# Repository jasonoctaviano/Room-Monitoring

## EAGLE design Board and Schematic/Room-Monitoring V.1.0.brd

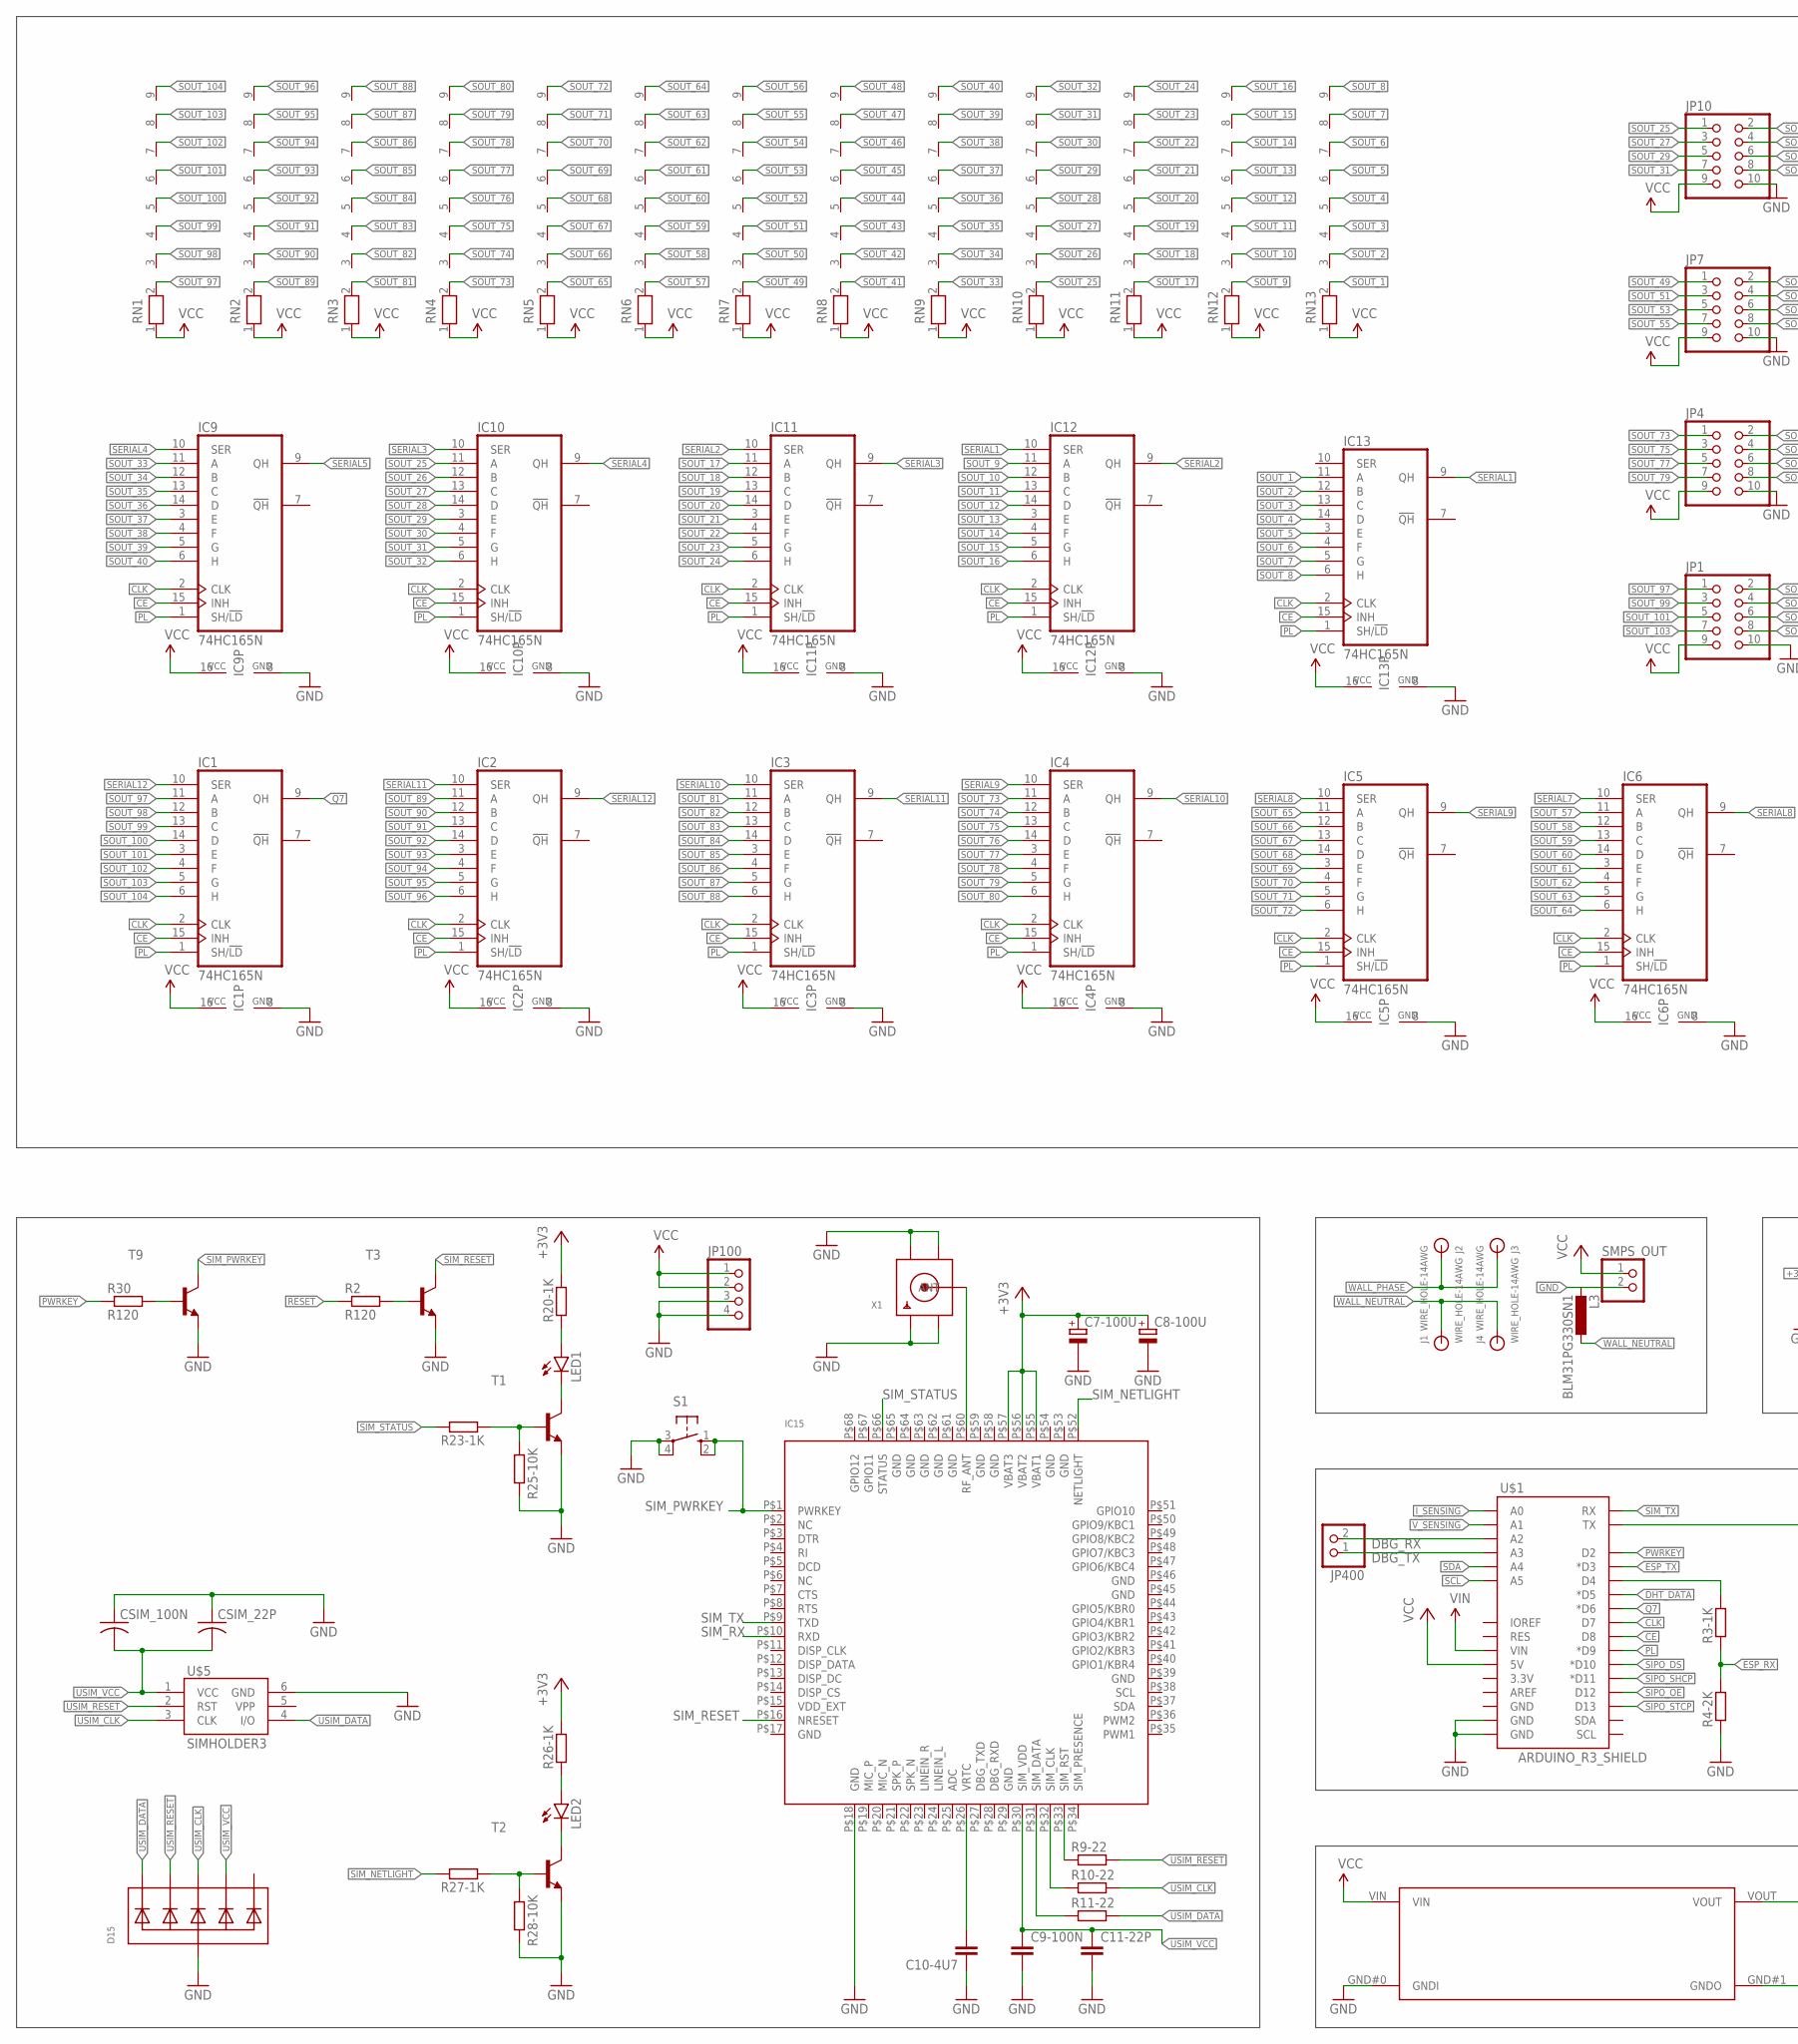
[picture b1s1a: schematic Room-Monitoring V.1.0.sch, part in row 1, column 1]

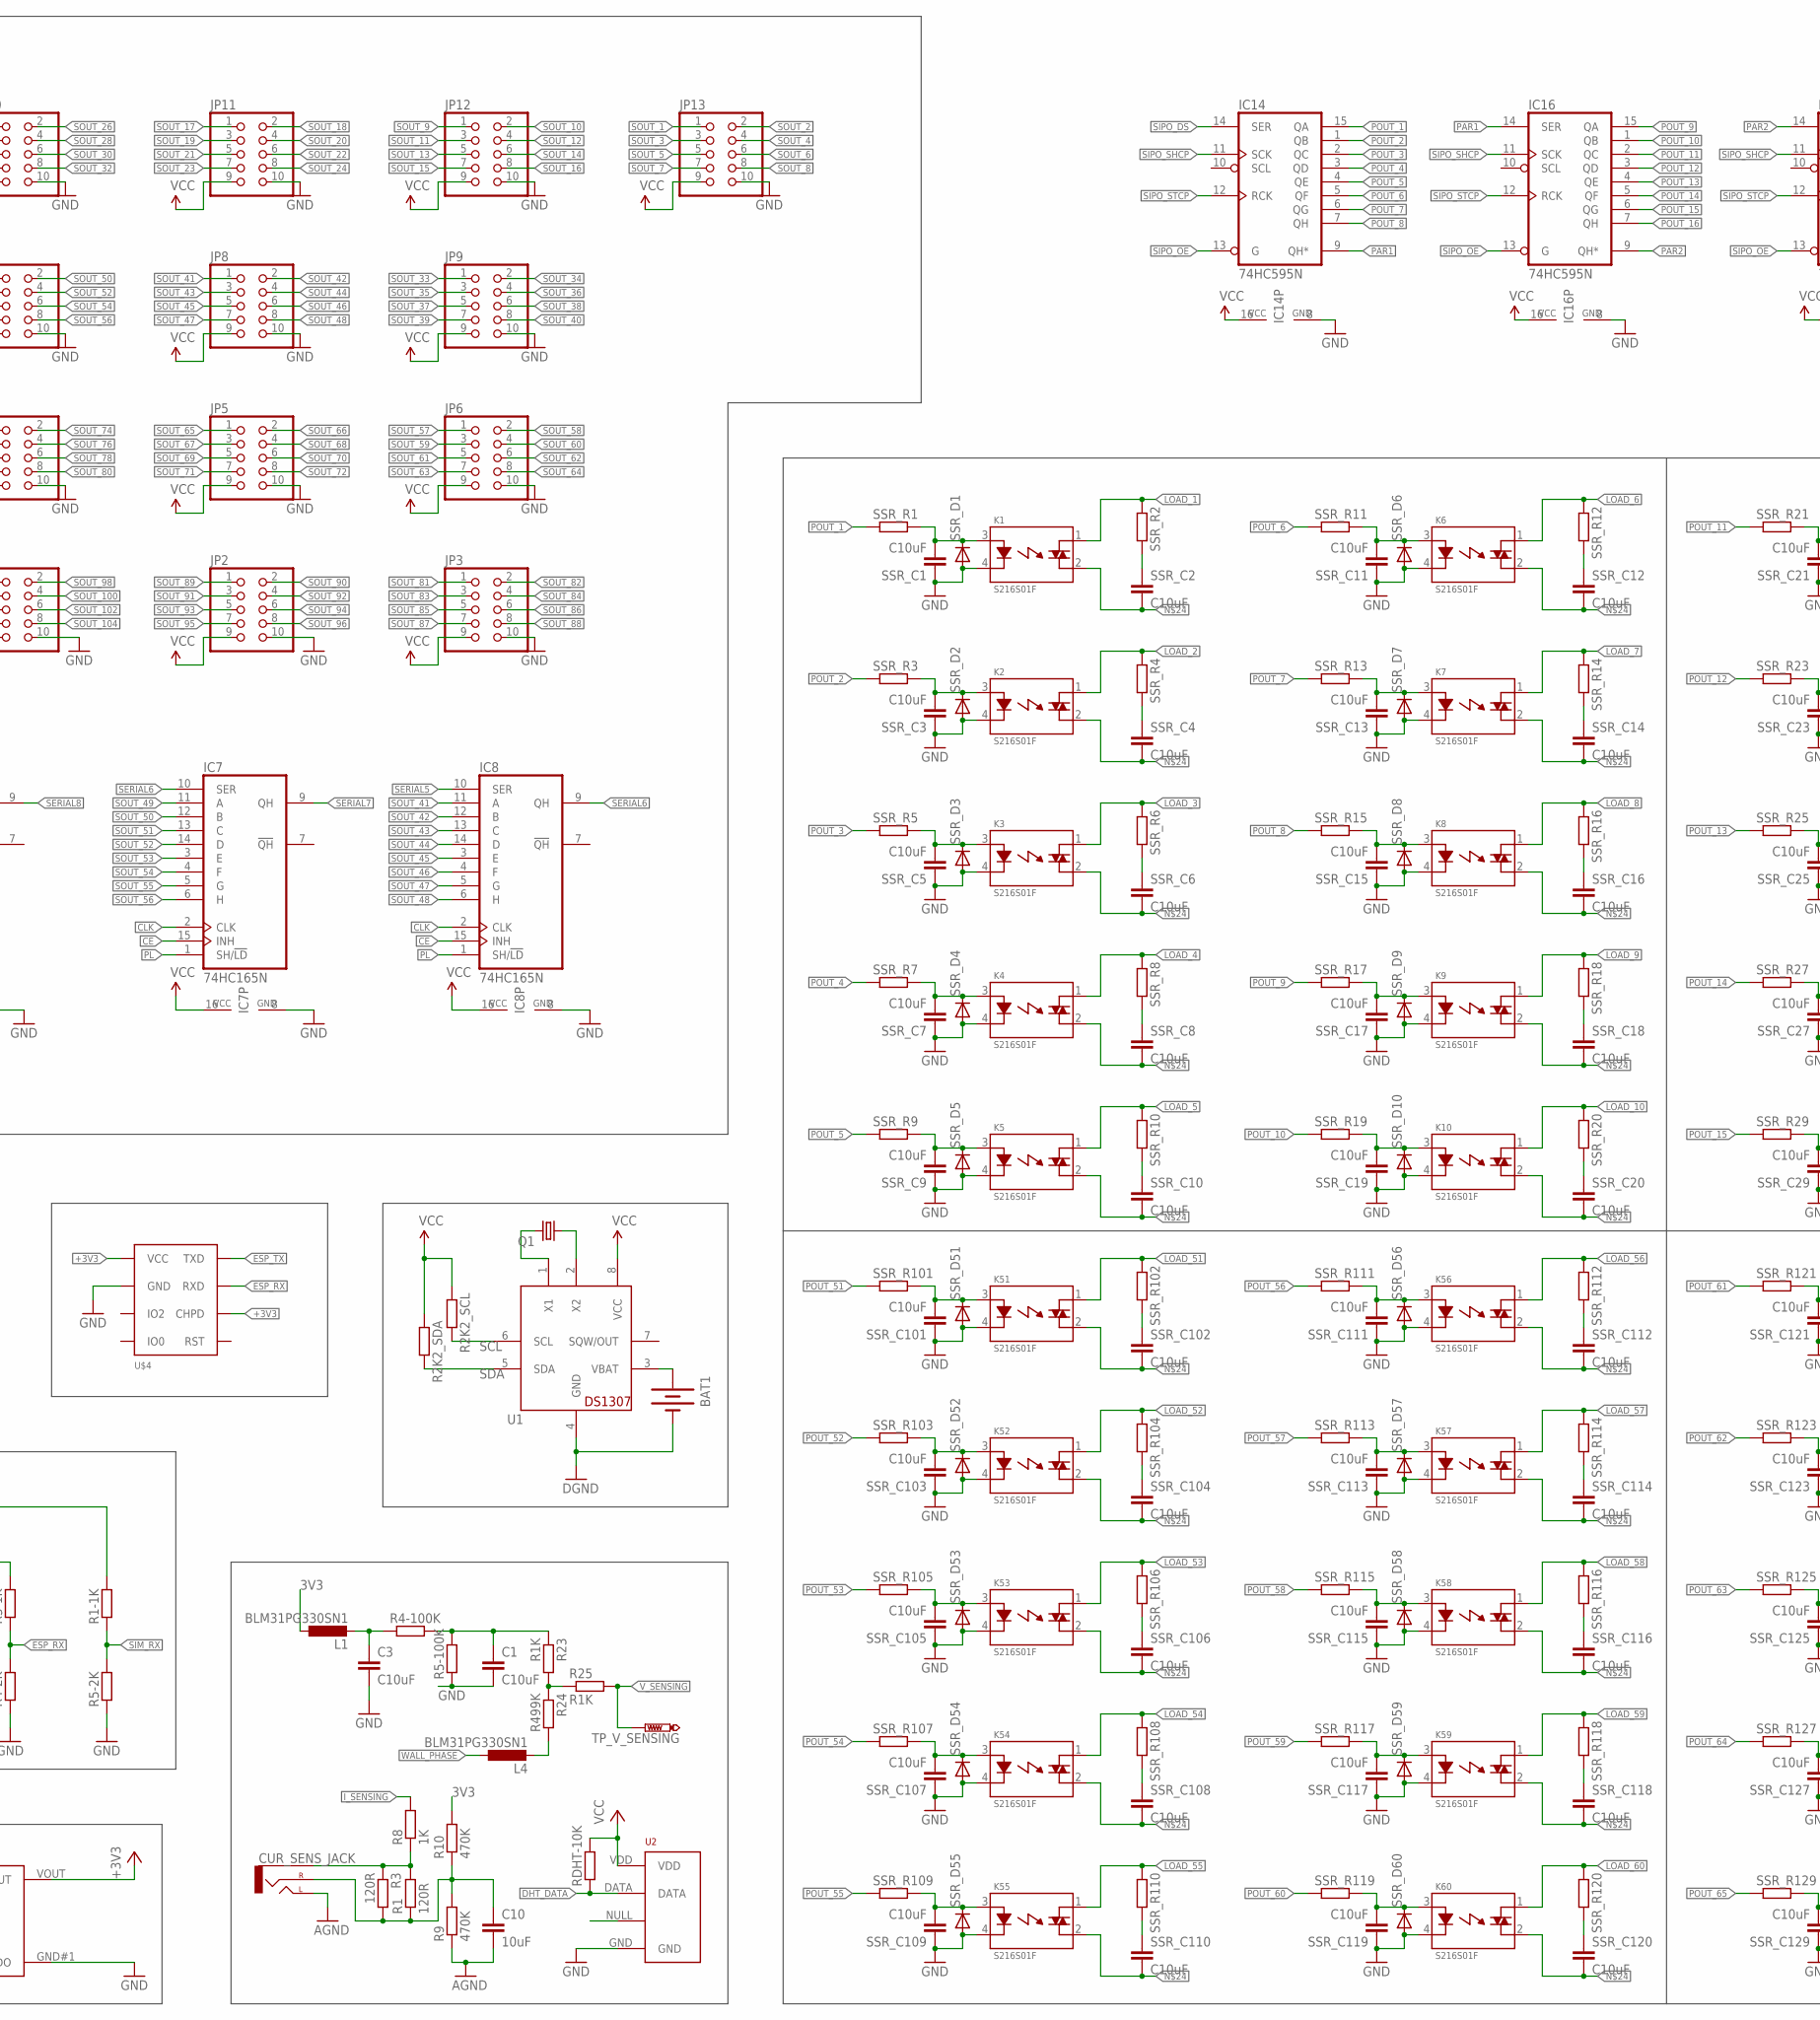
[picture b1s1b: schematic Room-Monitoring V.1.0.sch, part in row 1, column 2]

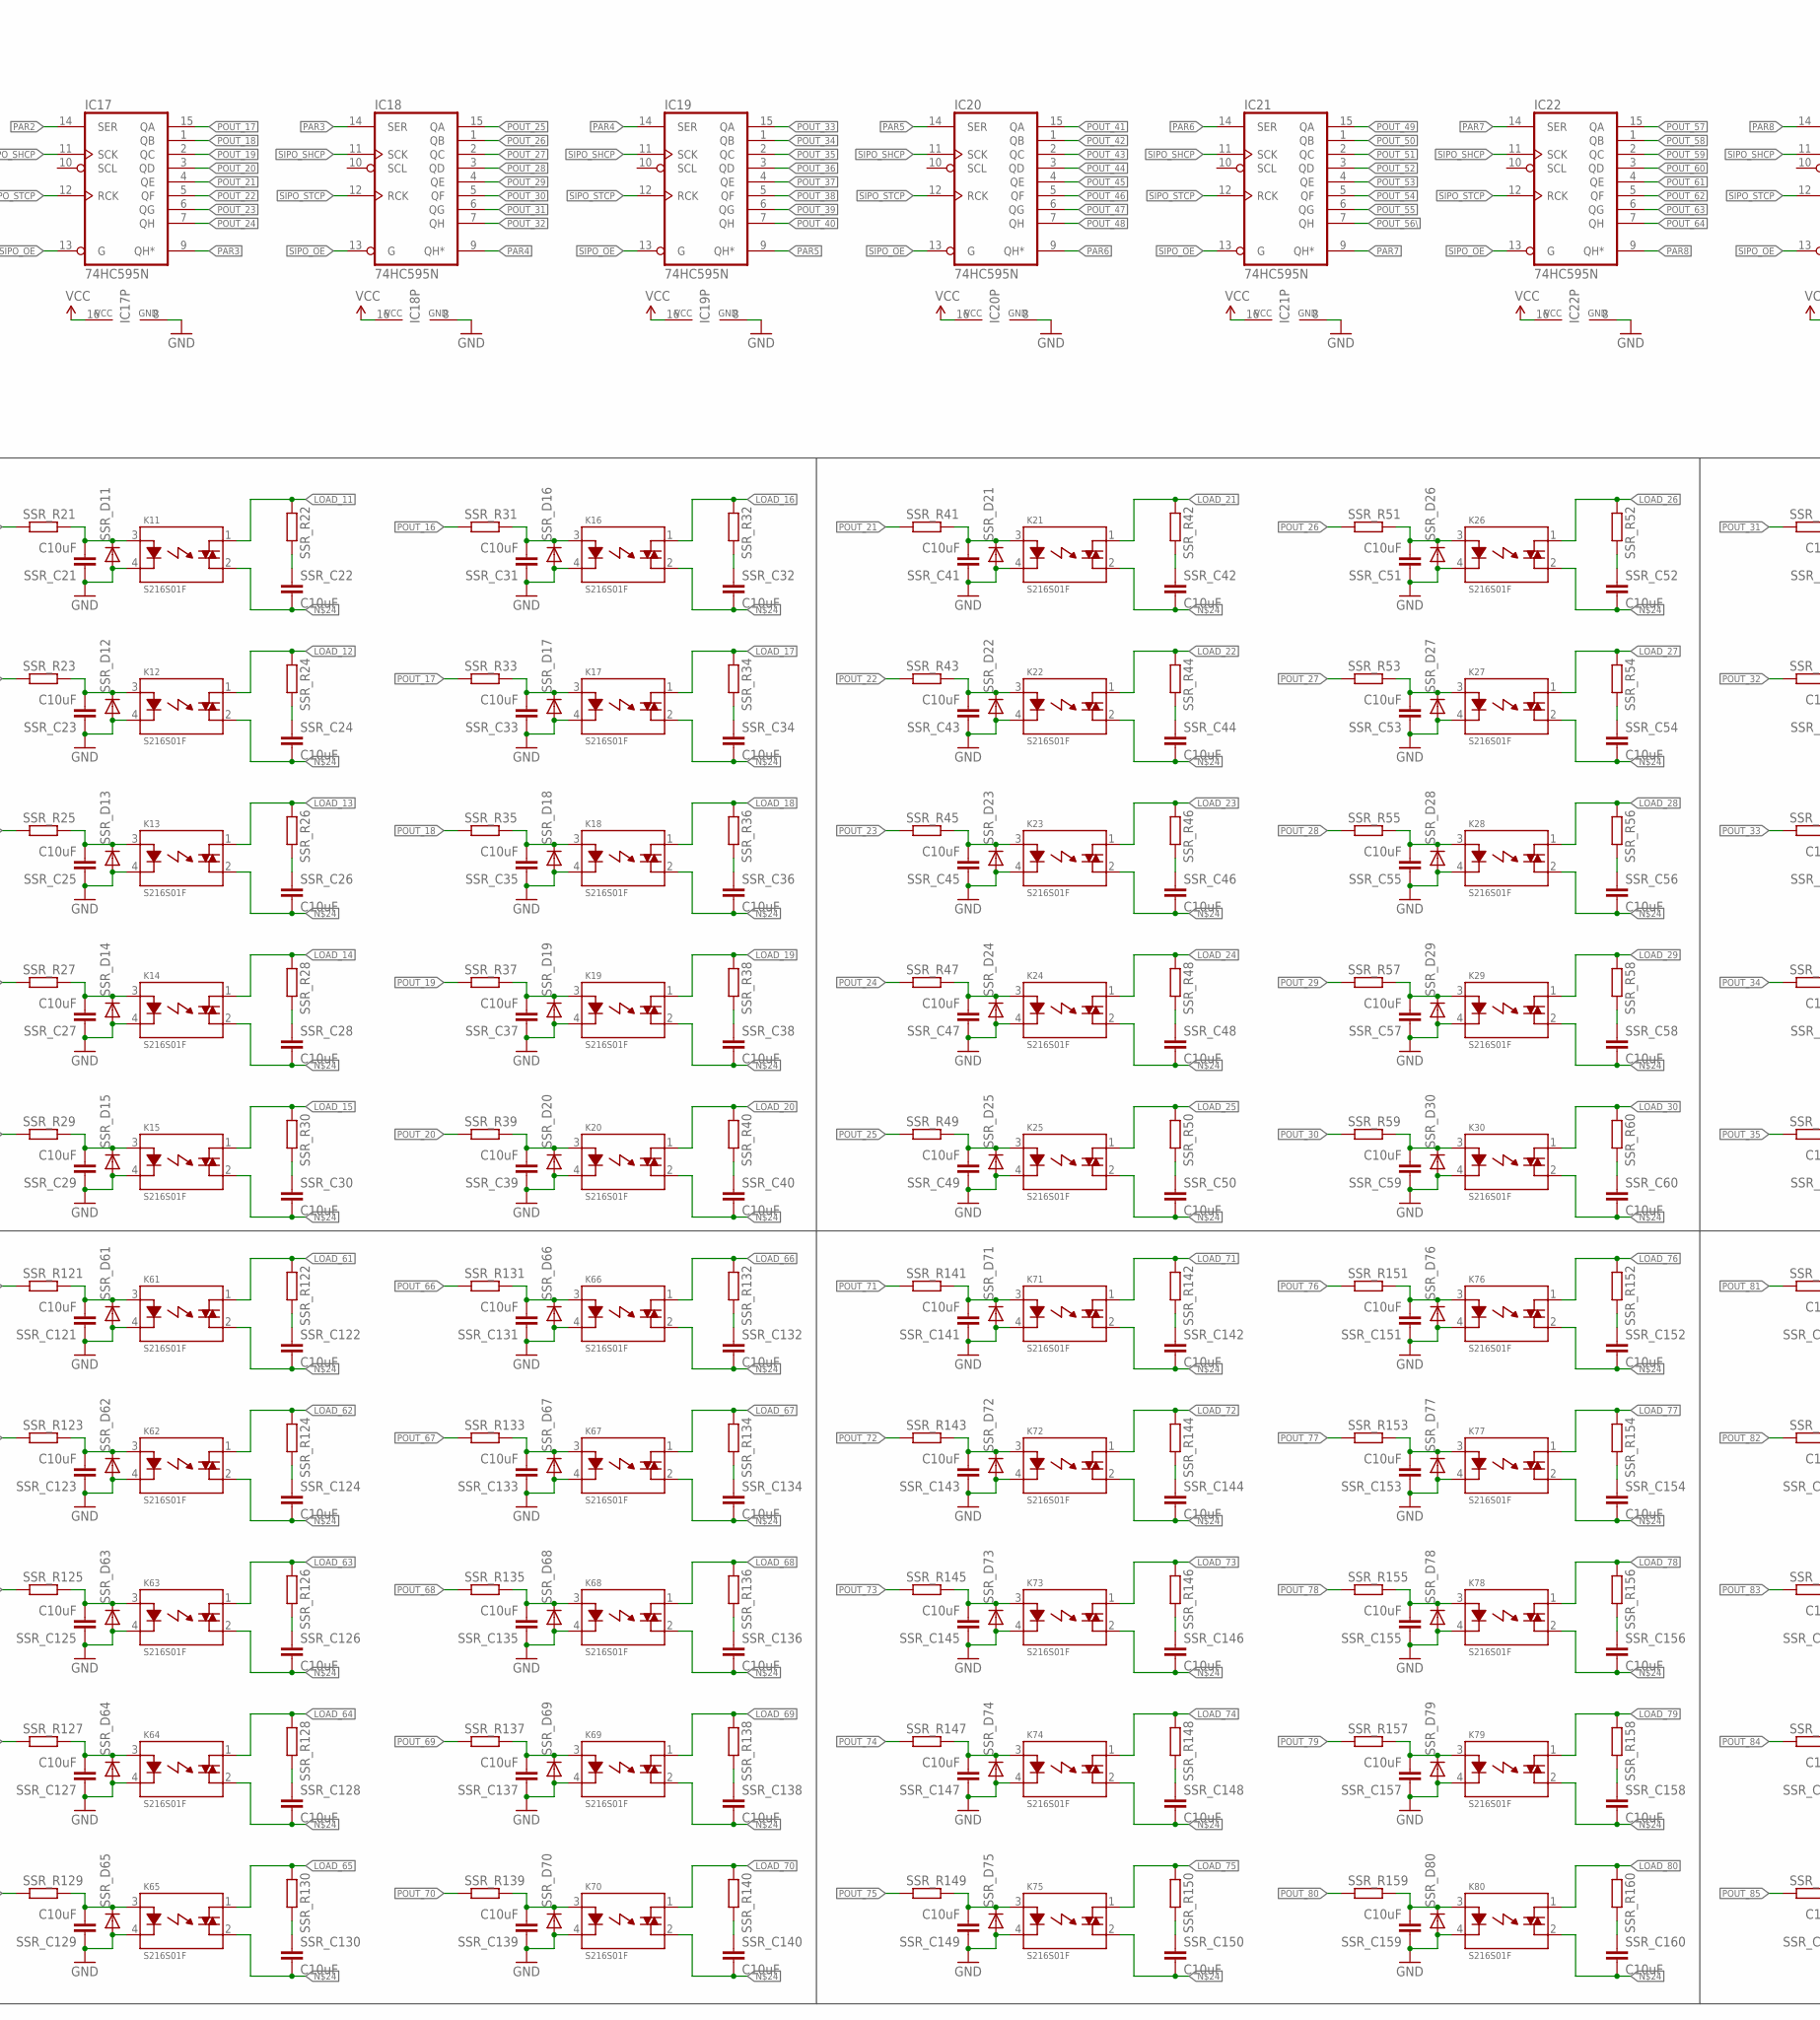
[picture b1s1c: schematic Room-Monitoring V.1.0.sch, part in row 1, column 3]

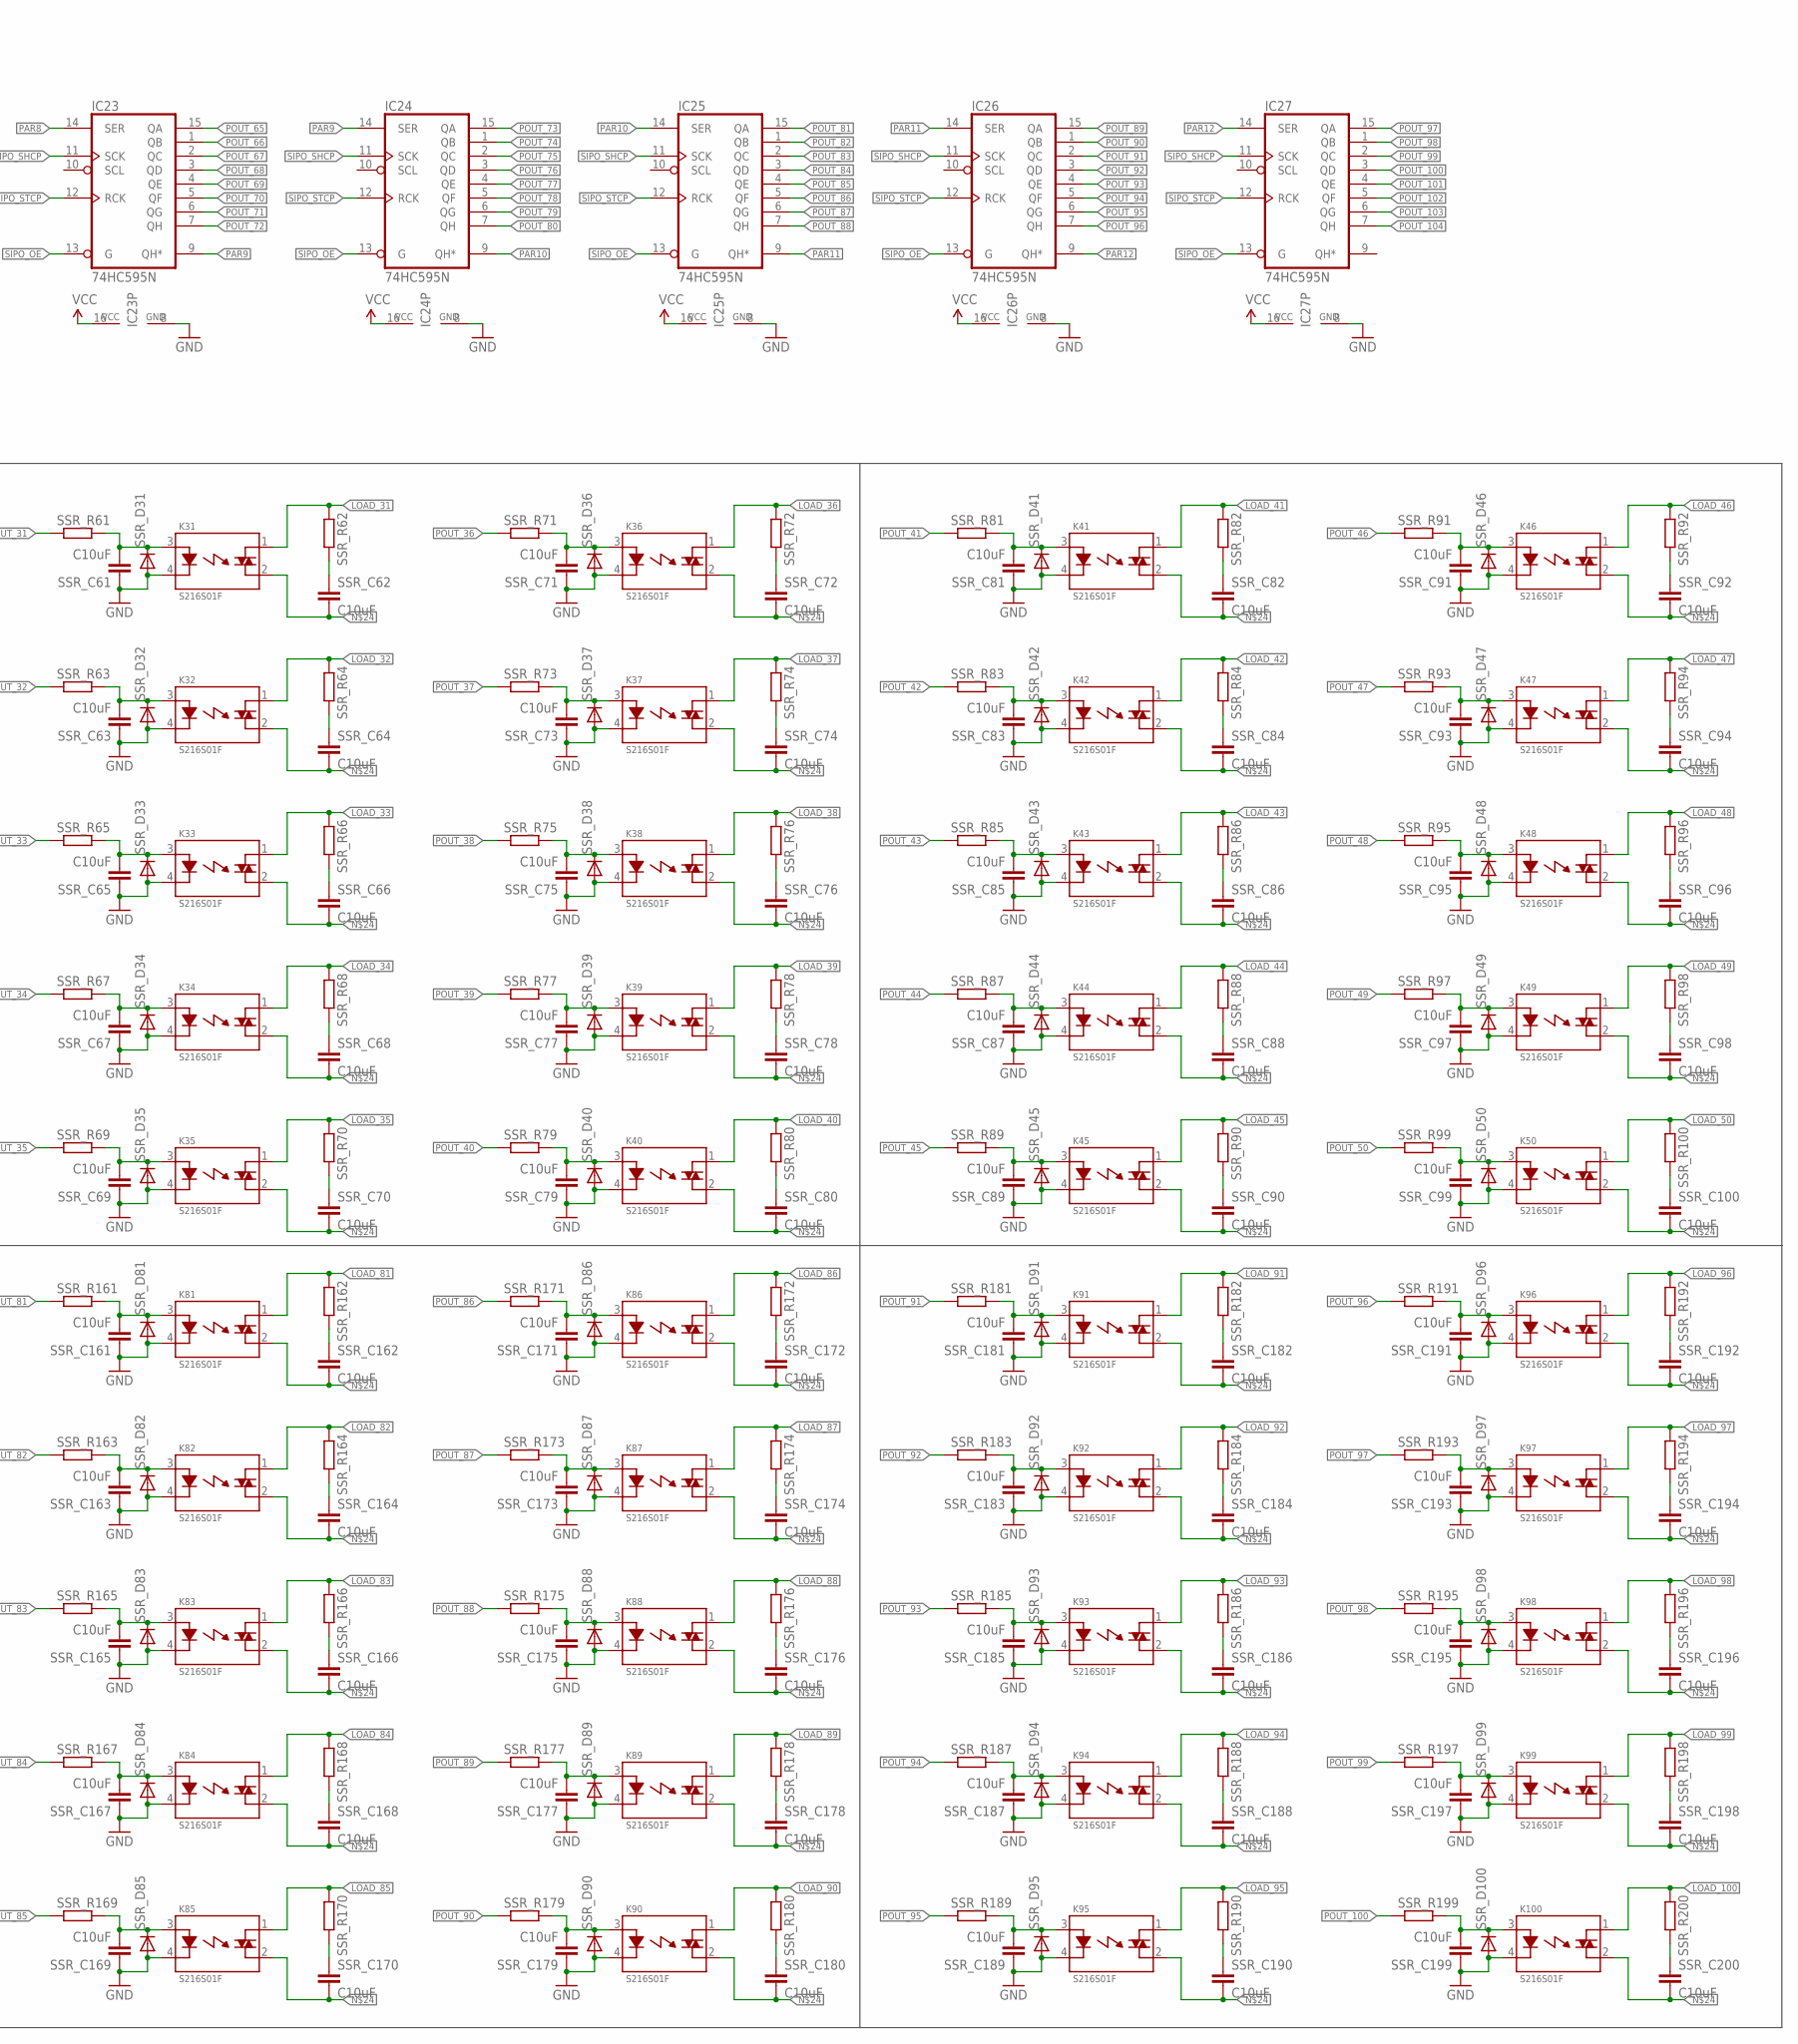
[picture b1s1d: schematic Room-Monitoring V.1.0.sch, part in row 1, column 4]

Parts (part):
BAT1: BATTERY20PTH; BATTCOM_20MM_PTH
C1, C3: C10uF; C0805
C7-100U, C8-100U: CPOL-EU153CLV-0605; 153CLV-0605
C9-100N, C10-4U7, C11-22P: C-EUC0603; C0603
C10: 10uF; C0805
CSIM_22P, CSIM_100N: C-USC0603K; C0603K
CUR_SENS_JACK: AUDIO-JACKSMD2; AUDIO-JACK-3.5MM-SMD
D15: TVSARRAY_5LANE; SOT363
IC1, IC2, IC3, IC4, IC5, IC6, IC7, IC8, IC9, IC10, IC11, IC12, IC13: 74HC165N; DIL16
IC14, IC16, IC17, IC18, IC19, IC20, IC21, IC22, IC23, IC24, IC25, IC26, IC27: 74HC595N; DIL16
IC15: GSM_SIM900_LITERAL; SIM900_SMT
J1, J2, J3, J4: WIRE_HOLE-14AWG
JP1, JP2, JP3, JP4, JP5, JP6, JP7, JP8, JP9, JP10, JP11, JP12, JP13: PINHD-2X5; 2X05
JP100: PINHD-1X4; 1X04
JP400: PINHD-1X2; 1X02
K1, K2, K3, K4, K5, K6, K7, K8, K9, K10, K11, K12, K13, K14, K15, K16, K17, K18, K19, K20, K21, K22, K23, K24, K25, K26, K27, K28, K29, K30, K31, K32, K33, K34, K35, K36, K37, K38, K39, K40, K41, K42, K43, K44, K45, K46, K47, K48, K49, K50, K51, K52, K53, K54, K55, K56, K57, K58, K59, K60, K61, K62, K63, K64, K65, K66, K67, K68, K69, K70, K71, K72, K73, K74, K75, K76, K77, K78, K79, K80, K81, K82, K83, K84, K85, K86, K87, K88, K89, K90, K91, K92, K93, K94, K95, K96, K97, K98, K99, K100: S216S01F; RELAY_SX16S0X
L1, L3, L4: BLM31PG330SN1; L3216C
LED1, LED2: LED-3MM-NO_SILK; LED3MM-NS
Q1: CRYSTALTC26H; TC26H
R1: 120R; 0204/7
R1-1K, R2K2_SCL, R2K2_SDA, R3-1K, R4-2K, R5-2K, R9-22, R10-22, R11-22, R20-1K, R23-1K, R25-10K, R26-1K, R27-1K, R28-10K: R-EU_R0603; R0603
R2, R30: R120; M0805
R3: 120R; R1206
R4-100K, R5-100K: R-EU_R0805; R0805
R8: 1K; R0805
R9, R10: 470K; R0805
R23, R25: R1K; R0805
R24: R499K; R0805
RDHT-10K: R-EU_R0603; R0603
RN1, RN2, RN3, RN4, RN5, RN6, RN7, RN8, RN9, RN10, RN11, RN12, RN13: RN08; RN-9
S1: 10-XX; B3F-10XX
SMPS_OUT: PINHD-1X2; 1X02
SSR_C1, SSR_C2, SSR_C3, SSR_C4, SSR_C5, SSR_C6, SSR_C7, SSR_C8, SSR_C9, SSR_C10, SSR_C11, SSR_C12, SSR_C13, SSR_C14, SSR_C15, SSR_C16, SSR_C17, SSR_C18, SSR_C19, SSR_C20, SSR_C21, SSR_C22, SSR_C23, SSR_C24, SSR_C25, SSR_C26, SSR_C27, SSR_C28, SSR_C29, SSR_C30, SSR_C31, SSR_C32, SSR_C33, SSR_C34, SSR_C35, SSR_C36, SSR_C37, SSR_C38, SSR_C39, SSR_C40, SSR_C41, SSR_C42, SSR_C43, SSR_C44, SSR_C45, SSR_C46, SSR_C47, SSR_C48, SSR_C49, SSR_C50, SSR_C51, SSR_C52, SSR_C53, SSR_C54, SSR_C55, SSR_C56, SSR_C57, SSR_C58, SSR_C59, SSR_C60, SSR_C61, SSR_C62, SSR_C63, SSR_C64, SSR_C65, SSR_C66, SSR_C67, SSR_C68, SSR_C69, SSR_C70, SSR_C71, SSR_C72, SSR_C73, SSR_C74, SSR_C75, SSR_C76, SSR_C77, SSR_C78, SSR_C79, SSR_C80, SSR_C81, SSR_C82, SSR_C83, SSR_C84, SSR_C85, SSR_C86, SSR_C87, SSR_C88, SSR_C89, SSR_C90, SSR_C91, SSR_C92, SSR_C93, SSR_C94, SSR_C95, SSR_C96, SSR_C97, SSR_C98, SSR_C99, SSR_C100, SSR_C101, SSR_C102, SSR_C103, SSR_C104, SSR_C105, SSR_C106, SSR_C107, SSR_C108, SSR_C109, SSR_C110, SSR_C111, SSR_C112, SSR_C113, SSR_C114, SSR_C115, SSR_C116, SSR_C117, SSR_C118, SSR_C119, SSR_C120, SSR_C121, SSR_C122, SSR_C123, SSR_C124, SSR_C125, SSR_C126, SSR_C127, SSR_C128, SSR_C129, SSR_C130, SSR_C131, SSR_C132, SSR_C133, SSR_C134, SSR_C135, SSR_C136, SSR_C137, SSR_C138, SSR_C139, SSR_C140, SSR_C141, SSR_C142, SSR_C143, SSR_C144, SSR_C145, SSR_C146, SSR_C147, SSR_C148, SSR_C149, SSR_C150, SSR_C151, SSR_C152, SSR_C153, SSR_C154, SSR_C155, SSR_C156, SSR_C157, SSR_C158, SSR_C159, SSR_C160, SSR_C161, SSR_C162, SSR_C163, SSR_C164, SSR_C165, SSR_C166, SSR_C167, SSR_C168, SSR_C169, SSR_C170, SSR_C171, SSR_C172, SSR_C173, SSR_C174, SSR_C175, SSR_C176, SSR_C177, SSR_C178, SSR_C179, SSR_C180, SSR_C181, SSR_C182, SSR_C183, SSR_C184, SSR_C185, SSR_C186, SSR_C187, SSR_C188, SSR_C189, SSR_C190, SSR_C191, SSR_C192, SSR_C193, SSR_C194, SSR_C195, SSR_C196, SSR_C197, SSR_C198, SSR_C199, SSR_C200: C10uF; C0805
SSR_D1, SSR_D2, SSR_D3, SSR_D4, SSR_D5, SSR_D6, SSR_D7, SSR_D8, SSR_D9, SSR_D10, SSR_D11, SSR_D12, SSR_D13, SSR_D14, SSR_D15, SSR_D16, SSR_D17, SSR_D18, SSR_D19, SSR_D20, SSR_D21, SSR_D22, SSR_D23, SSR_D24, SSR_D25, SSR_D26, SSR_D27, SSR_D28, SSR_D29, SSR_D30, SSR_D31, SSR_D32, SSR_D33, SSR_D34, SSR_D35, SSR_D36, SSR_D37, SSR_D38, SSR_D39, SSR_D40, SSR_D41, SSR_D42, SSR_D43, SSR_D44, SSR_D45, SSR_D46, SSR_D47, SSR_D48, SSR_D49, SSR_D50, SSR_D51, SSR_D52, SSR_D53, SSR_D54, SSR_D55, SSR_D56, SSR_D57, SSR_D58, SSR_D59, SSR_D60, SSR_D61, SSR_D62, SSR_D63, SSR_D64, SSR_D65, SSR_D66, SSR_D67, SSR_D68, SSR_D69, SSR_D70, SSR_D71, SSR_D72, SSR_D73, SSR_D74, SSR_D75, SSR_D76, SSR_D77, SSR_D78, SSR_D79, SSR_D80, SSR_D81, SSR_D82, SSR_D83, SSR_D84, SSR_D85, SSR_D86, SSR_D87, SSR_D88, SSR_D89, SSR_D90, SSR_D91, SSR_D92, SSR_D93, SSR_D94, SSR_D95, SSR_D96, SSR_D97, SSR_D98, SSR_D99, SSR_D100: DIODE-DO214AC; DO214AC
SSR_R1, SSR_R2, SSR_R3, SSR_R4, SSR_R5, SSR_R6, SSR_R7, SSR_R8, SSR_R9, SSR_R10, SSR_R11, SSR_R12, SSR_R13, SSR_R14, SSR_R15, SSR_R16, SSR_R17, SSR_R18, SSR_R19, SSR_R20, SSR_R21, SSR_R22, SSR_R23, SSR_R24, SSR_R25, SSR_R26, SSR_R27, SSR_R28, SSR_R29, SSR_R30, SSR_R31, SSR_R32, SSR_R33, SSR_R34, SSR_R35, SSR_R36, SSR_R37, SSR_R38, SSR_R39, SSR_R40, SSR_R41, SSR_R42, SSR_R43, SSR_R44, SSR_R45, SSR_R46, SSR_R47, SSR_R48, SSR_R49, SSR_R50, SSR_R51, SSR_R52, SSR_R53, SSR_R54, SSR_R55, SSR_R56, SSR_R57, SSR_R58, SSR_R59, SSR_R60, SSR_R61, SSR_R62, SSR_R63, SSR_R64, SSR_R65, SSR_R66, SSR_R67, SSR_R68, SSR_R69, SSR_R70, SSR_R71, SSR_R72, SSR_R73, SSR_R74, SSR_R75, SSR_R76, SSR_R77, SSR_R78, SSR_R79, SSR_R80, SSR_R81, SSR_R82, SSR_R83, SSR_R84, SSR_R85, SSR_R86, SSR_R87, SSR_R88, SSR_R89, SSR_R90, SSR_R91, SSR_R92, SSR_R93, SSR_R94, SSR_R95, SSR_R96, SSR_R97, SSR_R98, SSR_R99, SSR_R100, SSR_R101, SSR_R102, SSR_R103, SSR_R104, SSR_R105, SSR_R106, SSR_R107, SSR_R108, SSR_R109, SSR_R110, SSR_R111, SSR_R112, SSR_R113, SSR_R114, SSR_R115, SSR_R116, SSR_R117, SSR_R118, SSR_R119, SSR_R120, SSR_R121, SSR_R122, SSR_R123, SSR_R124, SSR_R125, SSR_R126, SSR_R127, SSR_R128, SSR_R129, SSR_R130, SSR_R131, SSR_R132, SSR_R133, SSR_R134, SSR_R135, SSR_R136, SSR_R137, SSR_R138, SSR_R139, SSR_R140, SSR_R141, SSR_R142, SSR_R143, SSR_R144, SSR_R145, SSR_R146, SSR_R147, SSR_R148, SSR_R149, SSR_R150, SSR_R151, SSR_R152, SSR_R153, SSR_R154, SSR_R155, SSR_R156, SSR_R157, SSR_R158, SSR_R159, SSR_R160, SSR_R161, SSR_R162, SSR_R163, SSR_R164, SSR_R165, SSR_R166, SSR_R167, SSR_R168, SSR_R169, SSR_R170, SSR_R171, SSR_R172, SSR_R173, SSR_R174, SSR_R175, SSR_R176, SSR_R177, SSR_R178, SSR_R179, SSR_R180, SSR_R181, SSR_R182, SSR_R183, SSR_R184, SSR_R185, SSR_R186, SSR_R187, SSR_R188, SSR_R189, SSR_R190, SSR_R191, SSR_R192, SSR_R193, SSR_R194, SSR_R195, SSR_R196, SSR_R197, SSR_R198, SSR_R199, SSR_R200: R-EU_R0603; R0603
T1, T2, T3, T9: MMBT2222ALT1-NPN-SOT23-BEC; SOT23-BEC
TP_V_SENSING: PTR1PAD1-13; P1-13
U1: DS1307; DIL08
U2: RHT03_DHT-22_AM2302; RHT03_DHT-22
U$1: ARDUINO_R3_SHIELD; UNO_R3_SHIELD
U$2: DCDCMODULE
U$4: ESP8266
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
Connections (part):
3V3: L1.1, R10.2
+3V3: C7-100U.+, C8-100U.+, IC15.P$55 (VBAT1), IC15.P$56 (VBAT2), IC15.P$57 (VBAT3), R20-1K.2, R26-1K.2, U$2.VOUT, U$4.CHPD, U$4.VCC
AGND: C10.2, CUR_SENS_JACK.TIP (LEFT), R9.1
CE: IC1.15 (INH), IC2.15 (INH), IC3.15 (INH), IC4.15 (INH), IC5.15 (INH), IC6.15 (INH), IC7.15 (INH), IC8.15 (INH), IC9.15 (INH), IC10.15 (INH), IC11.15 (INH), IC12.15 (INH), IC13.15 (INH), U$1.D8
CLK: IC1.2 (CLK), IC2.2 (CLK), IC3.2 (CLK), IC4.2 (CLK), IC5.2 (CLK), IC6.2 (CLK), IC7.2 (CLK), IC8.2 (CLK), IC9.2 (CLK), IC10.2 (CLK), IC11.2 (CLK), IC12.2 (CLK), IC13.2 (CLK), U$1.D7
DBG_RX: JP400.2, U$1.A2
DBG_TX: JP400.1, U$1.A3
DHT_DATA: RDHT-10K.1, U2.DATA, U$1.D5 (*D5)
ESP_RX: R3-1K.1, R4-2K.2, U$4.RXD
ESP_TX: U$1.D3 (*D3), U$4.TXD
GND: BAT1.2 (-), C1.2, C3.2, C7-100U.-, C8-100U.-, C9-100N.2, C10-4U7.1, C11-22P.2, CSIM_22P.1, CSIM_100N.1, D15.2 (A), IC1.8 (GND), IC2.8 (GND), IC3.8 (GND), IC4.8 (GND), IC5.8 (GND), IC6.8 (GND), IC7.8 (GND), IC8.8 (GND), IC9.8 (GND), IC10.8 (GND), IC11.8 (GND), IC12.8 (GND), IC13.8 (GND), IC14.8 (GND), IC15.P$17 (GND), IC15.P$18 (GND), IC15.P$29 (GND), IC15.P$39 (GND), IC15.P$45 (GND), IC15.P$46 (GND), IC15.P$53 (GND), IC15.P$54 (GND), IC15.P$58 (GND), IC15.P$59 (GND), IC15.P$61 (GND), IC15.P$62 (GND), IC15.P$63 (GND), IC15.P$64 (GND), IC15.P$65 (GND), IC16.8 (GND), IC17.8 (GND), IC18.8 (GND), IC19.8 (GND), IC20.8 (GND), IC21.8 (GND), IC22.8 (GND), IC23.8 (GND), IC24.8 (GND), IC25.8 (GND), IC26.8 (GND), IC27.8 (GND), JP1.10, JP2.10, JP3.10, JP4.10, JP5.10, JP6.10, JP7.10, JP8.10, JP9.10, JP10.10, JP11.10, JP12.10, JP13.10, JP100.3, JP100.4, K1.4, K2.4, K3.4, K4.4, K5.4, K6.4, K7.4, K8.4, K9.4, K10.4, K11.4, K12.4, K13.4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
GPIO11: IC15.P$67 (GPIO11)
GPIO12: IC15.P$68 (GPIO12)
I_SENSING: R8.2, U$1.A0
LOAD_1: K1.1, SSR_R2.1
LOAD_2: K2.1, SSR_R4.1
LOAD_3: K3.1, SSR_R6.1
LOAD_4: K4.1, SSR_R8.1
LOAD_5: K5.1, SSR_R10.1
LOAD_6: K6.1, SSR_R12.1
LOAD_7: K7.1, SSR_R14.1
LOAD_8: K8.1, SSR_R16.1
LOAD_9: K9.1, SSR_R18.1
LOAD_10: K10.1, SSR_R20.1
LOAD_11: K11.1, SSR_R22.1
LOAD_12: K12.1, SSR_R24.1
LOAD_13: K13.1, SSR_R26.1
LOAD_14: K14.1, SSR_R28.1
LOAD_15: K15.1, SSR_R30.1
LOAD_16: K16.1, SSR_R32.1
LOAD_17: K17.1, SSR_R34.1
LOAD_18: K18.1, SSR_R36.1
LOAD_19: K19.1, SSR_R38.1
LOAD_20: K20.1, SSR_R40.1
LOAD_21: K21.1, SSR_R42.1
LOAD_22: K22.1, SSR_R44.1
LOAD_23: K23.1, SSR_R46.1
LOAD_24: K24.1, SSR_R48.1
LOAD_25: K25.1, SSR_R50.1
LOAD_26: K26.1, SSR_R52.1
LOAD_27: K27.1, SSR_R54.1
LOAD_28: K28.1, SSR_R56.1
LOAD_29: K29.1, SSR_R58.1
LOAD_30: K30.1, SSR_R60.1
LOAD_31: K31.1, SSR_R62.1
LOAD_32: K32.1, SSR_R64.1
LOAD_33: K33.1, SSR_R66.1
LOAD_34: K34.1, SSR_R68.1
LOAD_35: K35.1, SSR_R70.1
LOAD_36: K36.1, SSR_R72.1
LOAD_37: K37.1, SSR_R74.1
LOAD_38: K38.1, SSR_R76.1
LOAD_39: K39.1, SSR_R78.1
LOAD_40: K40.1, SSR_R80.1
LOAD_41: K41.1, SSR_R82.1
LOAD_42: K42.1, SSR_R84.1
LOAD_43: K43.1, SSR_R86.1
LOAD_44: K44.1, SSR_R88.1
LOAD_45: K45.1, SSR_R90.1
LOAD_46: K46.1, SSR_R92.1
LOAD_47: K47.1, SSR_R94.1
LOAD_48: K48.1, SSR_R96.1
LOAD_49: K49.1, SSR_R98.1
LOAD_50: K50.1, SSR_R100.1
LOAD_51: K51.1, SSR_R102.1
LOAD_52: K52.1, SSR_R104.1
LOAD_53: K53.1, SSR_R106.1
LOAD_54: K54.1, SSR_R108.1
LOAD_55: K55.1, SSR_R110.1
LOAD_56: K56.1, SSR_R112.1
LOAD_57: K57.1, SSR_R114.1
LOAD_58: K58.1, SSR_R116.1
LOAD_59: K59.1, SSR_R118.1
LOAD_60: K60.1, SSR_R120.1
LOAD_61: K61.1, SSR_R122.1
LOAD_62: K62.1, SSR_R124.1
LOAD_63: K63.1, SSR_R126.1
LOAD_64: K64.1, SSR_R128.1
LOAD_65: K65.1, SSR_R130.1
LOAD_66: K66.1, SSR_R132.1
LOAD_67: K67.1, SSR_R134.1
LOAD_68: K68.1, SSR_R136.1
LOAD_69: K69.1, SSR_R138.1
LOAD_70: K70.1, SSR_R140.1
LOAD_71: K71.1, SSR_R142.1
LOAD_72: K72.1, SSR_R144.1
LOAD_73: K73.1, SSR_R146.1
LOAD_74: K74.1, SSR_R148.1
LOAD_75: K75.1, SSR_R150.1
LOAD_76: K76.1, SSR_R152.1
LOAD_77: K77.1, SSR_R154.1
LOAD_78: K78.1, SSR_R156.1
LOAD_79: K79.1, SSR_R158.1
LOAD_80: K80.1, SSR_R160.1
LOAD_81: K81.1, SSR_R162.1
LOAD_82: K82.1, SSR_R164.1
LOAD_83: K83.1, SSR_R166.1
LOAD_84: K84.1, SSR_R168.1
LOAD_85: K85.1, SSR_R170.1
LOAD_86: K86.1, SSR_R172.1
LOAD_87: K87.1, SSR_R174.1
LOAD_88: K88.1, SSR_R176.1
LOAD_89: K89.1, SSR_R178.1
LOAD_90: K90.1, SSR_R180.1
LOAD_91: K91.1, SSR_R182.1
LOAD_92: K92.1, SSR_R184.1
LOAD_93: K93.1, SSR_R186.1
LOAD_94: K94.1, SSR_R188.1
LOAD_95: K95.1, SSR_R190.1
LOAD_96: K96.1, SSR_R192.1
LOAD_97: K97.1, SSR_R194.1
LOAD_98: K98.1, SSR_R196.1
LOAD_99: K99.1, SSR_R198.1
LOAD_100: K100.1, SSR_R200.1
unnamed: C3.1, L1.2, R4-100K.1
unnamed: IC15.P$32 (SIM_CLK), R10-22.1
unnamed: IC15.P$31 (SIM_DATA), R11-22.1
unnamed: IC15.P$33 (SIM_RST), R9-22.1
unnamed: C10-4U7.2, IC15.P$26 (VRTC)
unnamed: IC15.P$60 (RF_ANT), X1.ANTENNA (ANT)
unnamed: R1-1K.2, U$1.TX
unnamed: LED1.A, R20-1K.1
unnamed: LED1.K (C), T1.C
unnamed: R23-1K.1, R25-10K.1, T1.B
unnamed: LED2.A, R26-1K.1
unnamed: LED2.K (C), T2.C
unnamed: R27-1K.1, R28-10K.1, T2.B
unnamed: R30.2, T9.B
unnamed: R2.2, T3.B
unnamed: Q1.1, U1.2 (X2)
unnamed: R3-1K.2, U$1.D4
unnamed: Q1.2, U1.1 (X1)
unnamed: C1.1, R4-100K.2, R5-100K.2, R23.1
unnamed: R23.2, R24.1, R25.1
unnamed: L4.2, R24.2
unnamed: BAT1.1 (+), U1.3 (VBAT)
unnamed: K1.2, K2.2, K3.2, K4.2, K5.2, K6.2, K7.2, K8.2, K9.2, K10.2, K11.2, K12.2, K13.2, K14.2, K15.2, K16.2, K17.2, K18.2, K19.2, K20.2, K21.2, K22.2, K23.2, K24.2, K25.2, K26.2, K27.2, K28.2, K29.2, K30.2, K31.2, K32.2, K33.2, K34.2, K35.2, K36.2, K37.2, K38.2, K39.2, K40.2, K41.2, K42.2, K43.2, K44.2, K45.2, K46.2, K47.2, K48.2, K49.2, K50.2, K51.2, K52.2, K53.2, K54.2, K55.2, K56.2, K57.2, K58.2, K59.2, K60.2, K61.2, K62.2, K63.2, K64.2, K65.2, K66.2, K67.2, K68.2, K69.2, K70.2, K71.2, K72.2, K73.2, K74.2, K75.2, K76.2, K77.2, K78.2, K79.2, K80.2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
unnamed: CUR_SENS_JACK.SLEEVE, R1.2, R3.1, R8.1
unnamed: C10.1, CUR_SENS_JACK.RING (RIGHT), R1.1, R3.2, R9.2, R10.1
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
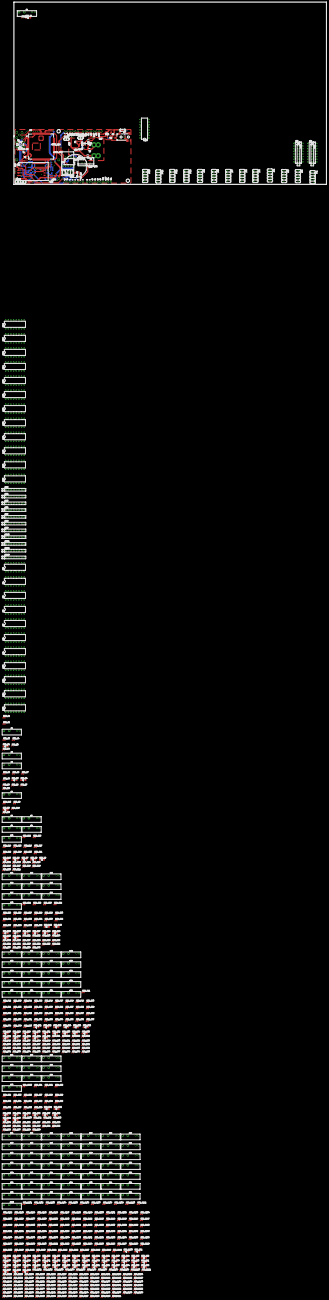
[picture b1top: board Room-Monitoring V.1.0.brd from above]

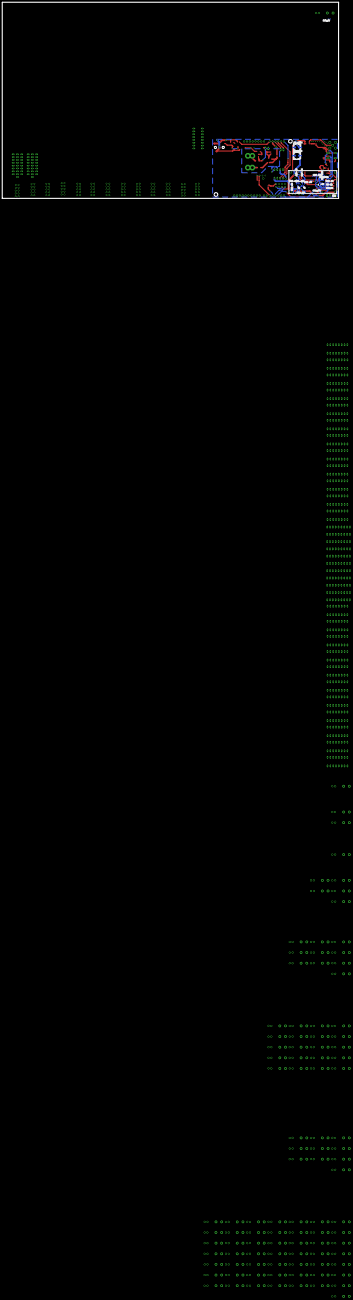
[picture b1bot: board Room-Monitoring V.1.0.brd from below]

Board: 2 copper layers, 300.4 x 175.2 mm, 720 parts (21 on the bottom side), 587 nets.

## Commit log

2015-07-02 Added Board and Schematic
    Board and Schematic are yet to be done and still in progress to be
    complete
2015-07-02 Added document literature
    shift register and ssr protection
2015-07-02 s216s01
    s216s01

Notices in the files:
parts and their libraries:
SparkFun-Boards: Licensing: Creative Commons ShareAlike 4.0 International - https://creativecommons.org/licenses/by-sa/4.0
SparkFun: Licensing: CC v3.0 Share-Alike You are welcome to use this library for commercial purposes.
